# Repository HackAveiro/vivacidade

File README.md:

Interactive LED wall
====================
This project is being developed to be installed in a public space in Aveiro that was recovered by a wide group of public and citizens entities. [vivacidade.umnovolargo.pt!](http://vivacidade.umnovolargo.pt)  
The interactive wall has 100 LEDs mounted in jam jars ! Each bottle has an RGB LED ( Neopixel ) and LDR sensor for users to physically interact with the wall. The panel is controlled by an Arduino which uses a radio link to communicate with a gateway situated a few hundred meters away and connects the system to the Internet. Because the place has no available electricity or Internet access it's powered by solar panels.  
Users can interact with the system through the Web App: [vivacidade-ledmatrixcontroller!](https://github.com/HackAveiro/vivacidade-ledmatrixcontroller)

Prototype images
===================

GIT Structure
=============

[ADC_BOARD!](ADC_Board)
===========
The system have 10 of this boards to connect all the 100 LED. The ADC board also have ADC chips that convert the LDR light sensors readings. The ADC chips are connected to the Arduino main board via a SPI bus.

PCB Schematic (Left Board)

PCB Layout ( (Left Board)

PCB Schematic (Left Board)

PCB Layout ( (Left Board)

[Gateway_Vivacidade!](Gateway_Vivacidade)
==================
{{Citation needed}} 

[led_board!](led_board)
=========
{{Citation needed}} 

Arduino dependencies
====================
* MCP3008 - https://github.com/nodesign/MCP3008
* RF24 - https://github.com/maniacbug/RF24.git
* FastLED - https://github.com/FastLED/FastLED

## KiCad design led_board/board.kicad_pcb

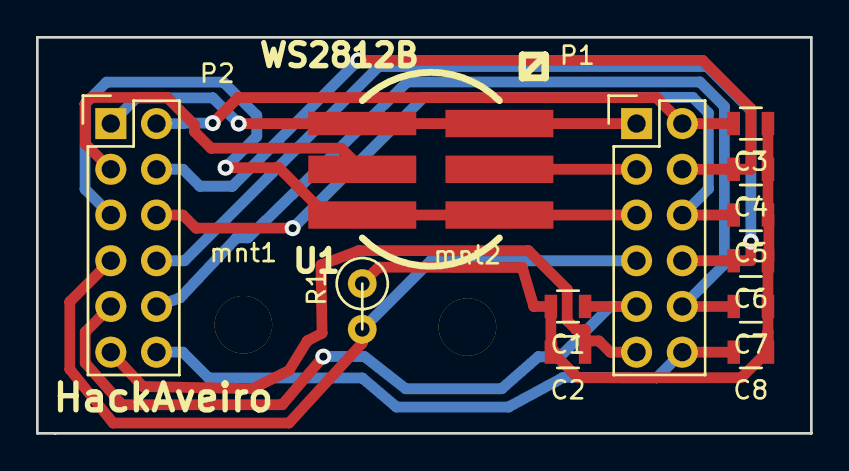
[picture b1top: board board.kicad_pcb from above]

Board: 2 copper layers, 43.0 x 22.0 mm, 14 parts (0 on the bottom side), 14 nets.

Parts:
C1, C2, C3, C4, C5, C6, C7, C8: C; R_0805
P1: INPUT; Pin_Header_Straight_2x06
P2: OUTPUT; Pin_Header_Straight_2x06
R1: RVAR; R1
U1: WS2812B; u
mnt1, mnt2: MountingHole_3mm

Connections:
Data_IN: P1.3, U1.2
Data_OUT: P2.3, U1.5
GND: P1.5, P2.5, U1.3, U1.4
LDR_GND: P1.7, P2.7, R1.2
LDR_OUT: C1.2, C2.2, C3.1, C4.1, C5.1, C6.1, C7.1, C8.1, R1.1
unnamed: C1.1, P1.9, P2.9
unnamed: C2.1, P1.11, P2.11
unnamed: C3.2, P1.2, P2.2
unnamed: C4.2, P1.4, P2.4
unnamed: C5.2, P1.6, P2.6
unnamed: C6.2, P1.8, P2.8
unnamed: C7.2, P1.10, P2.10
unnamed: C8.2, P1.12, P2.12
VCC: P1.1, P2.1, U1.1, U1.6

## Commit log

2015-06-24 moved
2015-06-24 dependencies
2015-07-08 Teste Matriz de 10 LED
    This code was tested with a 10 LED matrix.
    Protocol: RGB; HEX; ASCII; 6B x 10LED transmited
2015-07-22 added function to convert RGB string to binary 'string'
2015-08-12 changed server + autoack
2015-08-14 fixed sender
2015-08-14 merged receiver
2015-08-16 Complete rewrite
2015-08-19 Imagem
    Imagem criada para a submissão à MakerFaire.
2015-08-19 Adicionada Imagem
    A imagem submetida à candidatura da Maker Faire Lisbon.
2015-08-19 fixed and works
2015-08-27 added mapping function
2015-09-02 Adicionado esquema eléctrico das placas das ADCs
2015-09-02 Alterações ligeiras nos esquemas eléctricos das placas das ADCs.
2015-09-02 Mais formatos de imagens das placas das ADCs
2015-09-02 Led board Kicad source files
2015-09-02 adding led board schematic image file
2015-09-03 Revert "Update README.md"
    This reverts commit 073bfd32e43fffe96677afca54b6772b13c1df0b.
2015-09-03 Cleanup
2015-09-09 Documentação dos pinos de CS das placas das ADCs
2015-09-21 100 LEDs mapped
2015-10-13 Protótipo para uma shield para o arduino mega para ligar as placas "ADC_Board"
2016-03-30 Alterações ligeiras da documentaçao da ADC_Board
2016-03-30 Adicionado ficheiro '.gitignore' a pasta Arduino_Board
2016-03-30 Adicionado programa de teste dos LDRs via ADC_Board
2016-03-30 Adicionado mapa de ligações

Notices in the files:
led_board/board.kicad_pcb:
© 2015
